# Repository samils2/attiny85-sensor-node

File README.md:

# ATtiny85 Sensor Node

A small through-hole PCB built around an ATtiny85 that reads a potentiometer with the on-chip ADC and drives an LED output. I designed it in KiCad as the capstone of a self-directed electronics curriculum covering circuit fundamentals, digital logic, and PCB design workflow.

## Status

- [x] Schematic complete, ERC clean
- [x] PCB layout complete, DRC clean
- [x] Gerbers exported and ready for fabrication (JLCPCB)

<!-- Update this list as the project moves forward. Leave unchecked anything that is not done yet. -->

## Overview

The board has four main parts:

- **Sensor input:** a potentiometer wiper connected to PB3 (ADC3) for analog input
- **Output:** an LED driven by the microcontroller
- **Programming:** a 6-pin ISP header for flashing with a USBasp programmer
- **Power:** a decoupling capacitor, a RESET pull-up resistor, and a power indicator LED

I used through-hole components throughout so the board can be hand-soldered.

## Design Decisions

**Pin conflict between the potentiometer and SCK.** My first layout put the potentiometer wiper on a pin that also serves as SCK for in-system programming, which would have interfered with flashing the chip. I moved the wiper to PB3 so the ADC input and the ISP header no longer share a pin.

**Decoupling capacitor wiring.** While checking the schematic I found wiring errors in my decoupling capacitor connections and corrected them so the capacitor sits across the supply pins as intended.

**RESET pull-up.** I added a pull-up resistor on RESET so the chip does not reset from noise during normal operation.

**Power indicator LED.** I added an LED on the supply rail so I can confirm power with a quick glance before probing.

**Net labels for ISP routing.** I used net labels instead of long wires for the programming header connections to keep the schematic readable.

**Ground pour.** The board has a GND copper pour to give a low-impedance return path and simplify routing.

**Through-hole parts.** Every component is through-hole for easy hand-soldering.

## Bill of Materials

| Part | Notes |
|------|-------|
| ATtiny85-20PU | DIP-8 microcontroller |
| DIP-8 machined-pin socket | Lets the chip be removed and reprogrammed |
| Alpha RD901F-40 potentiometer | Analog input |
| 10 µF electrolytic capacitor | Decoupling Capacitor
| Pin headers | ISP programming header |
| LEDs and resistors | 330, 1k, & 10k Ω |
| USBasp programmer | For flashing (not part of the board) |

## Tools

- KiCad (schematic capture, PCB layout, DRC/ERC, Gerber export)
- JLCPCB (fabrication)
- USBasp (in-system programming)
- Multimeter (board testing)

## Author

Samil Sharma, Mechanical Engineering at UIUC (pursuing ECE) | https://www.linkedin.com/in/samil-sharma-a38b2a301/

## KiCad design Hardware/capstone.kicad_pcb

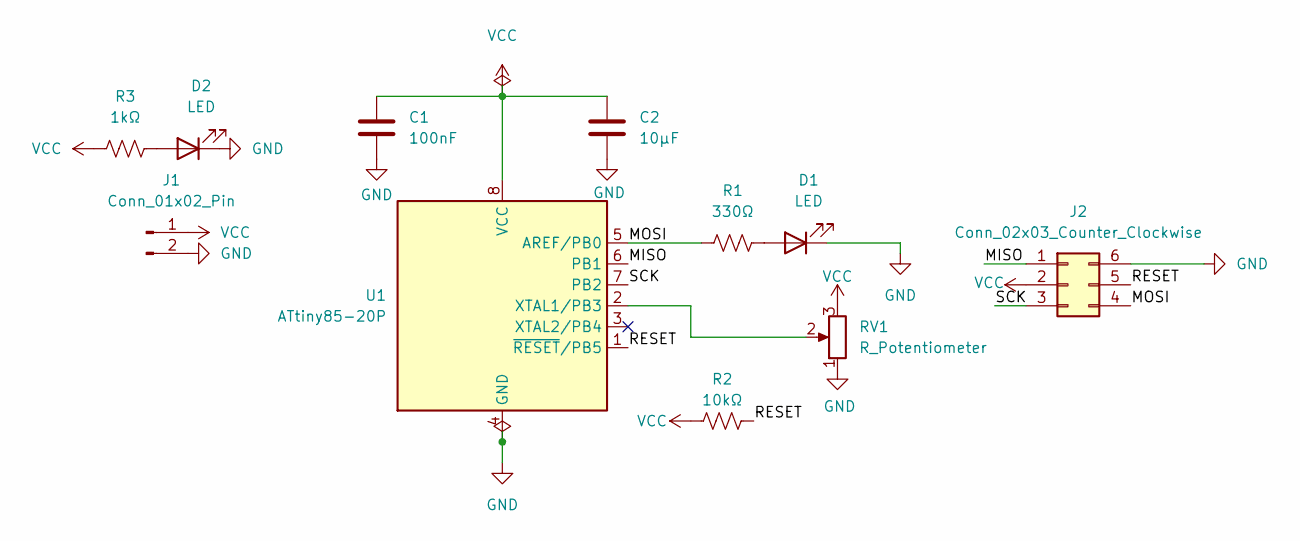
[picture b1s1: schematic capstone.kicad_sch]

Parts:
C1: 100nF; C_Disc_D3.0mm_W2.0mm_P2.50mm
C2: 10μF; CP_Radial_D5.0mm_P2.00mm
D1, D2: LED; LED_D5.0mm
J1: Conn_01x02_Pin; PinHeader_1x02_P2.54mm_Vertical
J2: Conn_02x03_Counter_Clockwise; PinHeader_2x03_P2.54mm_Vertical
R1: 330Ω; R_Axial_DIN0204_L3.6mm_D1.6mm_P7.62mm_Horizontal
R2: 10kΩ; R_Axial_DIN0204_L3.6mm_D1.6mm_P7.62mm_Horizontal
R3: 1kΩ; R_Axial_DIN0204_L3.6mm_D1.6mm_P7.62mm_Horizontal
RV1: R_Potentiometer; Potentiometer_Alpha_RD901F-40-00D_Single_Vertical_CircularH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
U1: ATtiny85-20P; DIP-8_W7.62mm_Socket

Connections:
/MISO: J2.1, U1.6 (PB1)
/MOSI: J2.4, R1.1, U1.5 (AREF/PB0)
/RESET: J2.5, R2.2, U1.1 (~RESET/PB5)
/SCK: J2.3, U1.7 (PB2)
GND: C1.2, C2.2, D1.1 (K), D2.1 (K), J1.2, J2.6, RV1.1, U1.4 (GND)
unnamed: D1.2 (A), R1.2
unnamed: D2.2 (A), R3.2
unnamed: RV1.2, U1.2 (XTAL1/PB3)
VCC: C1.1, C2.1, J1.1, J2.2, R2.1, R3.1, RV1.3, U1.8 (VCC)

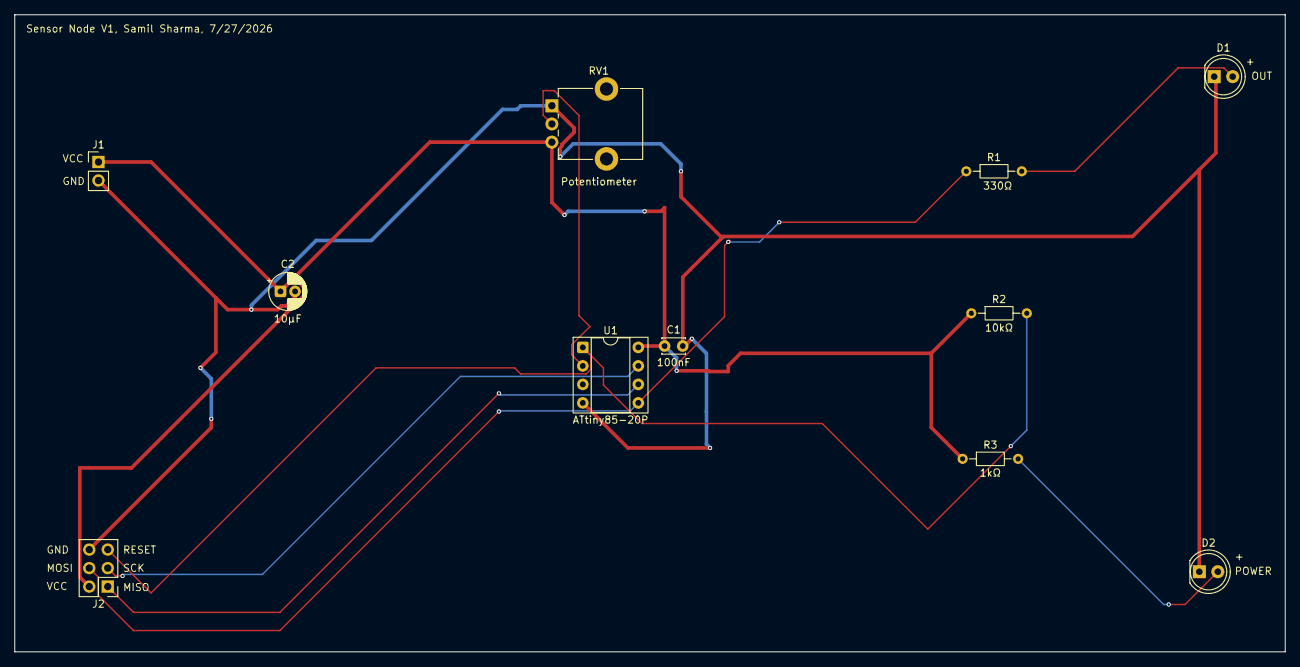
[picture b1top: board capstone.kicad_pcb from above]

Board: 2 copper layers, 174.5 x 87.5 mm, 11 parts (0 on the bottom side), 9 nets.
